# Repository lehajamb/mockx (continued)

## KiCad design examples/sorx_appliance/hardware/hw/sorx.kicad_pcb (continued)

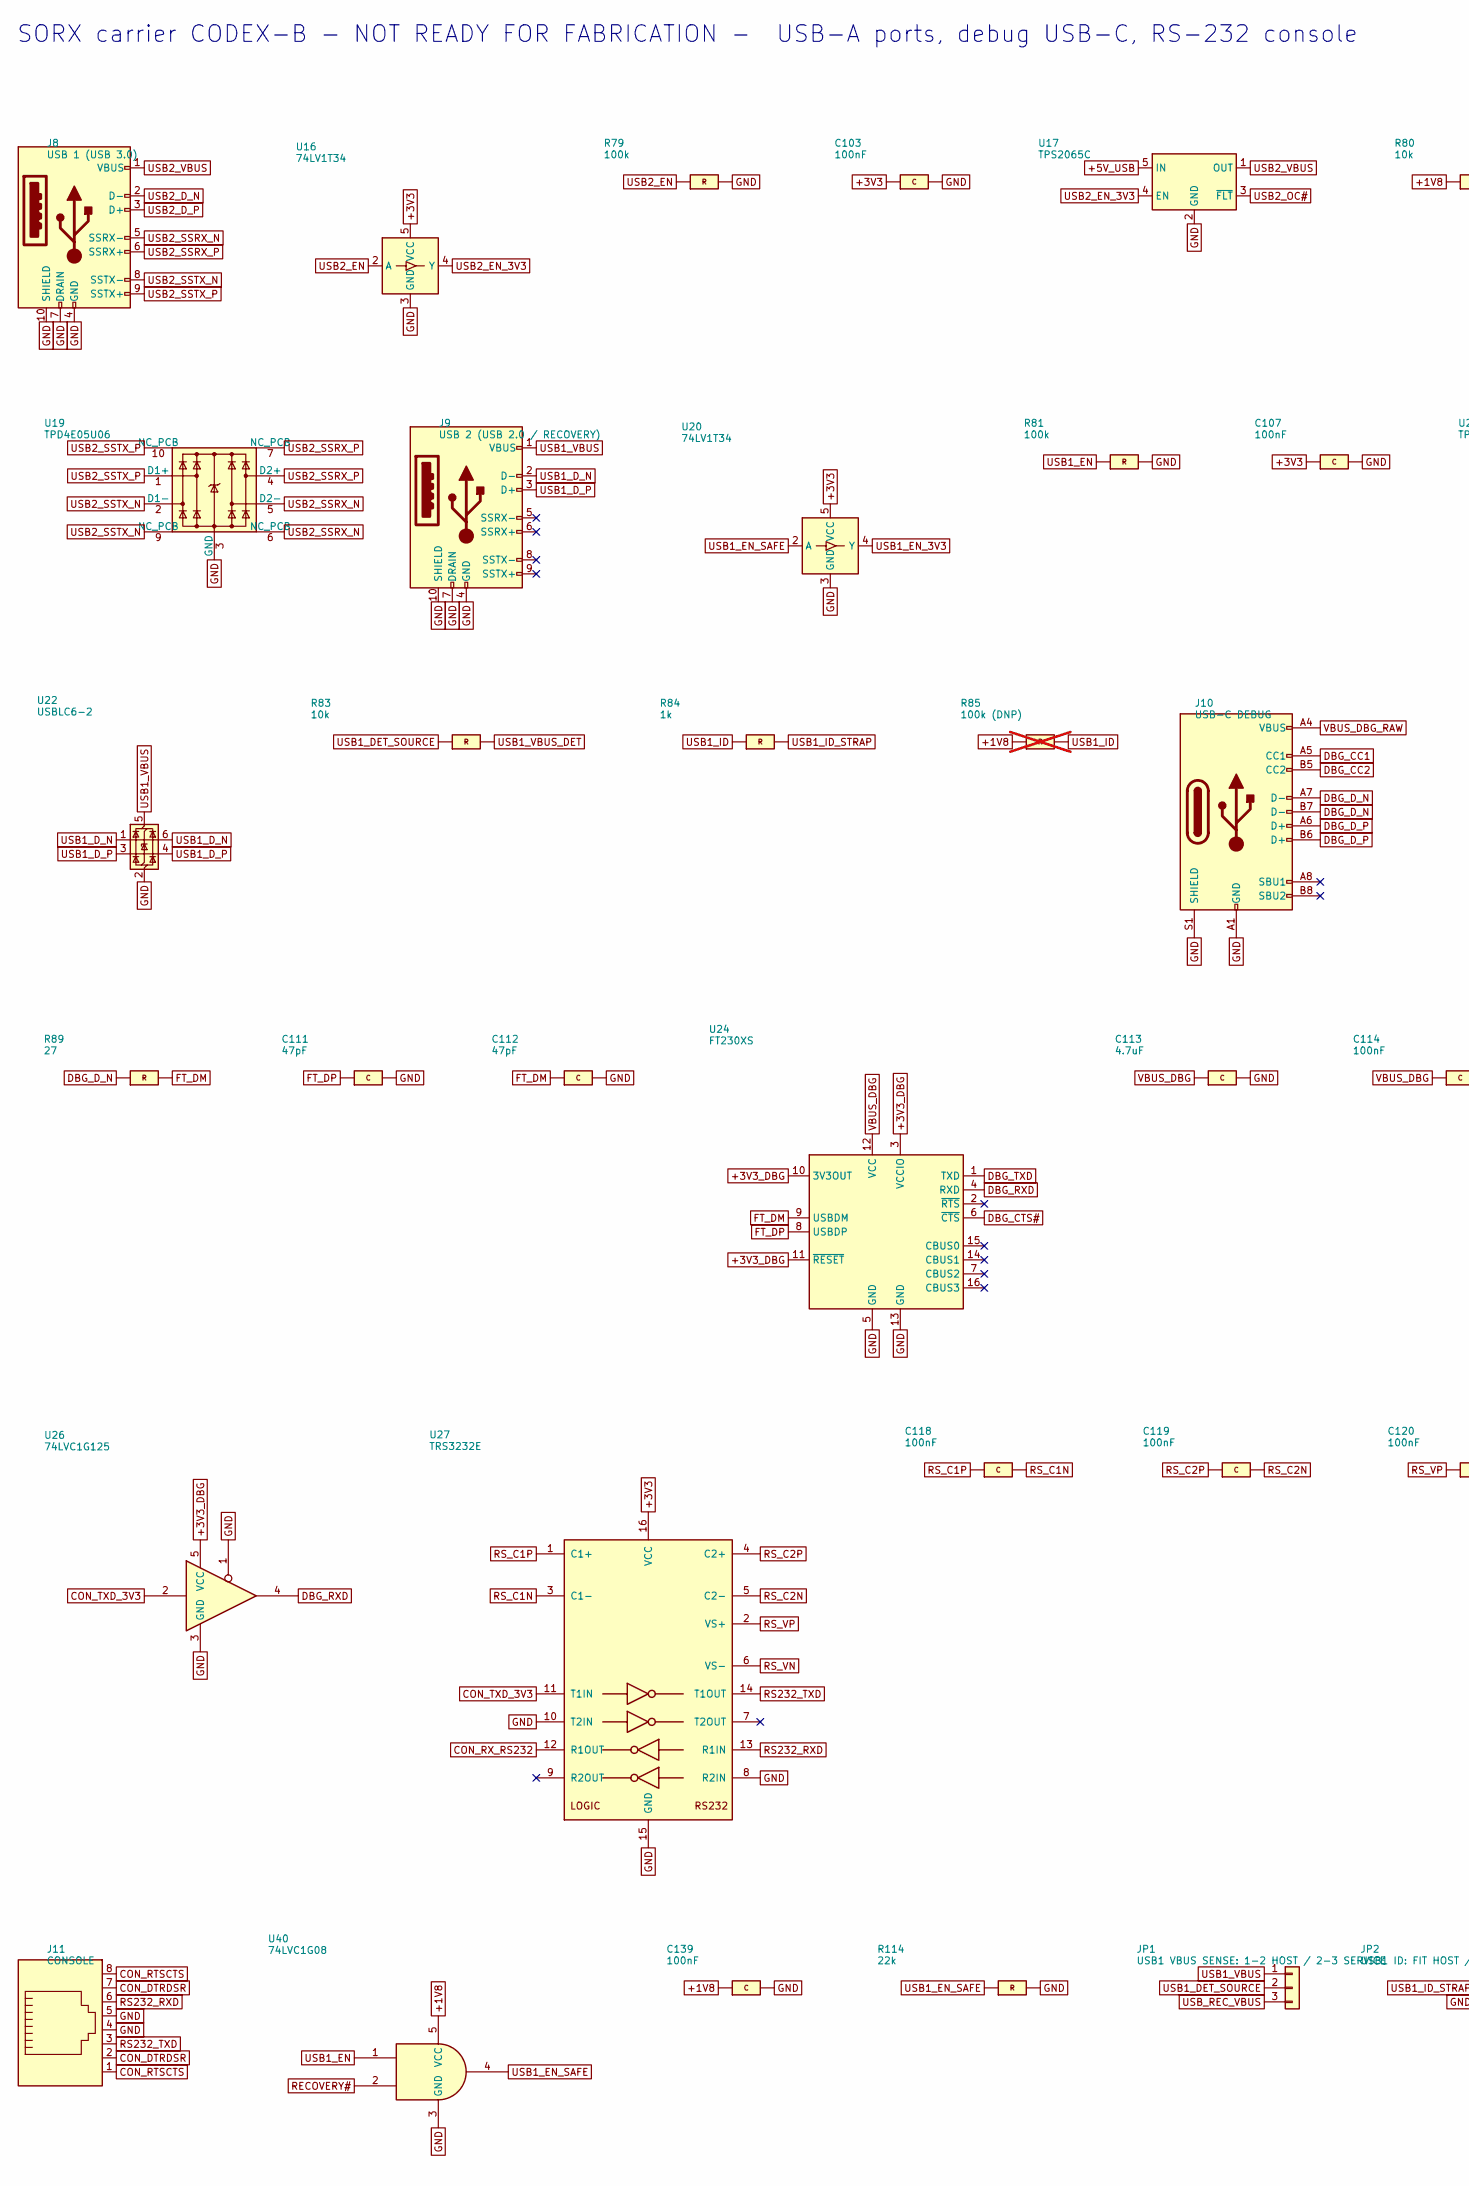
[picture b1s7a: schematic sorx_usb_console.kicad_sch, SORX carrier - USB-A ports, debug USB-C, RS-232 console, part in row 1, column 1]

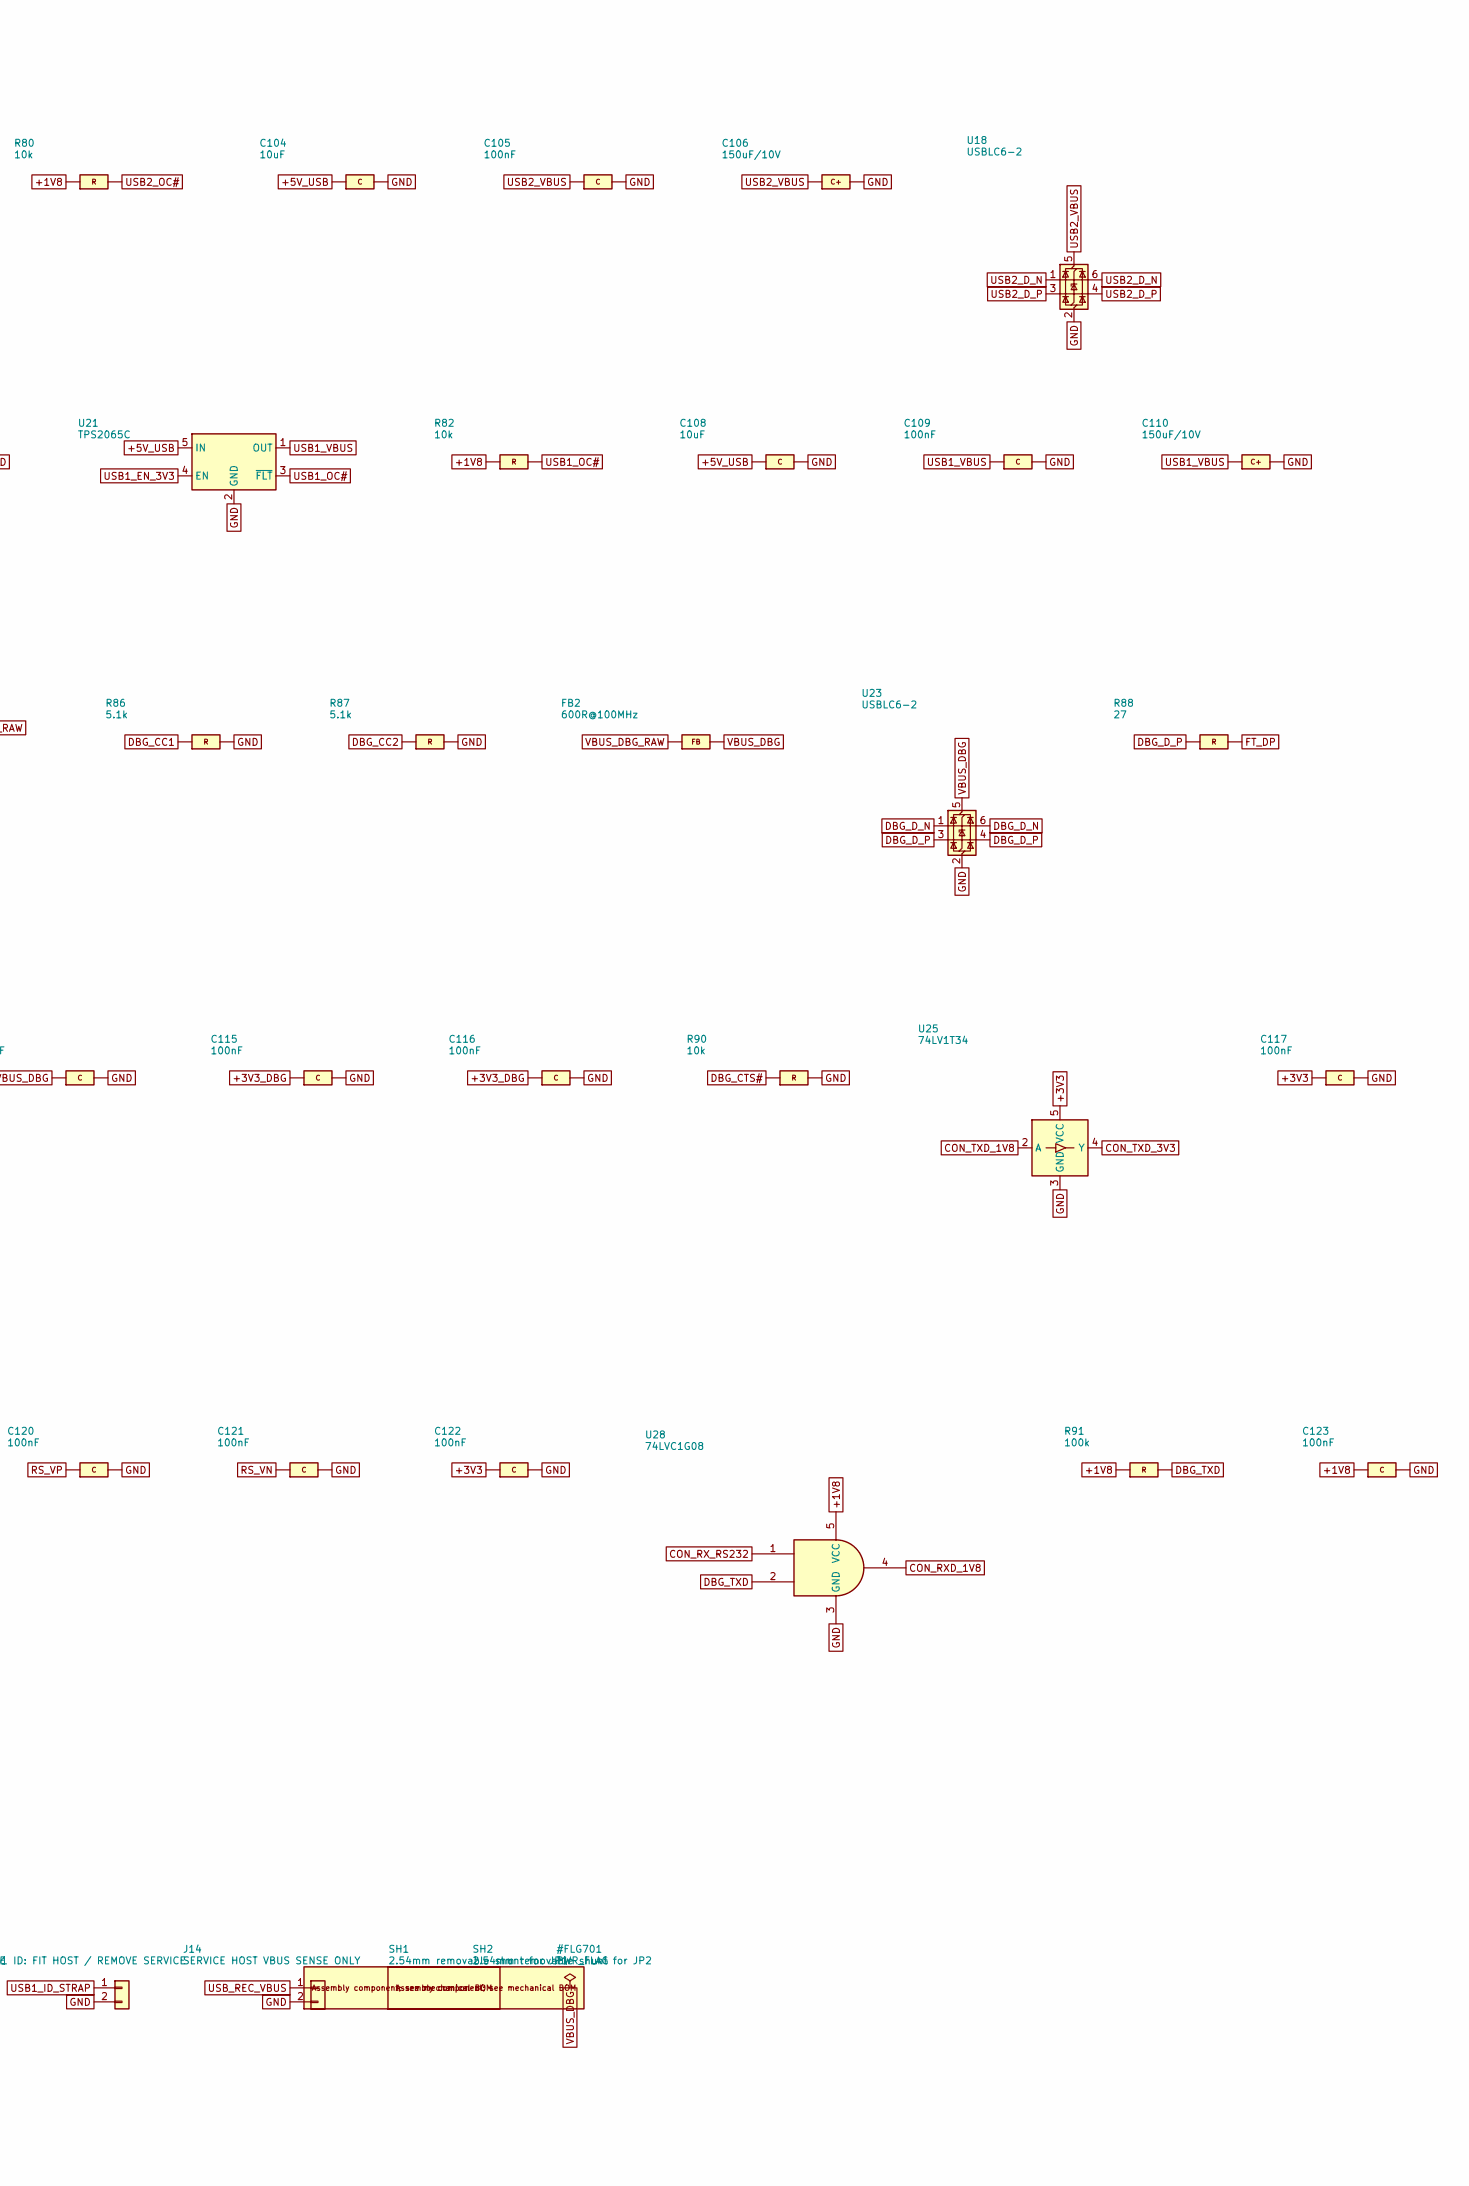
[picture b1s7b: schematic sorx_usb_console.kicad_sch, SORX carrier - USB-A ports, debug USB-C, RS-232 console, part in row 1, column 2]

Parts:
C103, C105, C107, C109, C114, C115, C116, C117, C118, C119, C120, C121, C122, C123, C139: 100nF; C_0402_1005Metric; MPN GRM155R71C104KA88D
C104, C108: 10uF; C_0805_2012Metric; MPN GRM21BR61A106KE19L
C106, C110: 150uF/10V; CP_Elec_6.3x7.7; MPN EEE-FK1A151P
C111, C112: 47pF; C_0402_1005Metric; MPN GRM1555C1H470JA01D
C113: 4.7uF; C_0603_1608Metric; MPN GRM188R61A475KE15D
FB2: 600R@100MHz; L_0603_1608Metric; MPN BLM18AG601SN1D
J8: USB 1 (USB 3.0); USB3_A_Receptacle_Wuerth_692122030100; MPN 692122030100
J9: USB 2 (USB 2.0 / RECOVERY); USB3_A_Receptacle_Wuerth_692122030100; MPN 692122030100
J10: USB-C DEBUG; USB_C_Receptacle_GCT_USB4105-xx-A_16P_TopMnt_Horizontal; MPN USB4105-GF-A
J11: CONSOLE; RJ45_Amphenol_54602-x08_Horizontal; MPN 54602-908LF
J14: SERVICE HOST VBUS SENSE ONLY; Wurth_61300211121; MPN 61300211121
JP1: USB1 VBUS SENSE: 1-2 HOST / 2-3 SERVICE; Wurth_61300311121; MPN 61300311121
JP2: USB1 ID: FIT HOST / REMOVE SERVICE; Wurth_61300211121; MPN 61300211121
R79, R81, R91: 100k; R_0402_1005Metric; MPN RC0402FR-07100KL
R80, R82, R83, R90: 10k; R_0402_1005Metric; MPN RC0402FR-0710KL
R84: 1k; R_0402_1005Metric; MPN RC0402FR-071KL
R85: 100k (DNP); R_0402_1005Metric; MPN RC0402FR-07100KL; not fitted
R86, R87: 5.1k; R_0402_1005Metric; MPN RC0402FR-075K1L
R88, R89: 27; R_0402_1005Metric; MPN RC0402FR-0727RL
R114: 22k; R_0402_1005Metric; MPN RC0402FR-0722KL
SH1: 2.54mm removable shunt for JP1; MPN 60900213421
SH2: 2.54mm removable shunt for JP2; MPN 60900213421
U16, U20, U25: 74LV1T34; SOT-23-5; MPN SN74LV1T34DBVR
U17, U21: TPS2065C; SOT-23-5; MPN TPS2065CDBVR
U18, U22, U23: USBLC6-2; SOT-23-6; MPN USBLC6-2SC6
U19: TPD4E05U06; USON-10_2.5x1.0mm_P0.5mm; MPN TPD4E05U06DQAR
U24: FT230XS; SSOP-16_3.9x4.9mm_P0.635mm; MPN FT230XS-R
U26: 74LVC1G125; SOT-23-5; MPN SN74LVC1G125DBVR
U27: TRS3232E; TSSOP-16_4.4x5mm_P0.65mm; MPN TRS3232EIPWR
U28, U40: 74LVC1G08; SOT-23-5; MPN SN74LVC1G08DBVR

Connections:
+1V8: C123.1, C139.1, R80.1, R82.1, R85.1, R91.1, U28.5 (VCC), U40.5 (VCC); also elsewhere on the board
+3V3: C103.1, C107.1, C117.1, C122.1, U16.5 (VCC), U20.5 (VCC), U25.5 (VCC), U27.16 (VCC); also elsewhere on the board
+3V3_DBG: C115.1, C116.1, U24.3 (VCCIO), U24.10 (3V3OUT), U24.11 (~RESET), U26.5 (VCC)
+5V_USB: C104.1, C108.1, U17.5 (IN), U21.5 (IN); also elsewhere on the board
CON_DTRDSR: J11.2, J11.7
CON_RTSCTS: J11.1, J11.8
CON_RXD_1V8: U28.4; also elsewhere on the board
CON_RX_RS232: U27.12 (R1OUT), U28.1
CON_TXD_1V8: U25.2 (A); also elsewhere on the board
CON_TXD_3V3: U25.4 (Y), U26.2, U27.11 (T1IN)
DBG_CC1: J10.A5 (CC1), R86.1
DBG_CC2: J10.B5 (CC2), R87.1
DBG_CTS#: R90.1, U24.6 (~CTS)
DBG_D_N: J10.A7 (D-), J10.B7 (D-), R89.1, U23.1 (I/O1), U23.6 (I/O1)
DBG_D_P: J10.A6 (D+), J10.B6 (D+), R88.1, U23.3 (I/O2), U23.4 (I/O2)
DBG_RXD: U24.4 (RXD), U26.4
DBG_TXD: R91.2, U24.1 (TXD), U28.2
FT_DM: C112.1, R89.2, U24.9 (USBDM)
FT_DP: C111.1, R88.2, U24.8 (USBDP)
GND: C103.2, C104.2, C105.2, C106.2 (-), C107.2, C108.2, C109.2, C110.2 (-), C111.2, C112.2, C113.2, C114.2, C115.2, C116.2, C117.2, C120.2, C121.2, C122.2, C123.2, C139.2, J8.4 (GND), J8.7 (DRAIN), J8.10 (SHIELD), J9.4 (GND), J9.7 (DRAIN), J9.10 (SHIELD), J10.A1 (GND), J10.A12 (GND), J10.B1 (GND), J10.B12 (GND), J10.S1 (SHIELD), J11.4, J11.5, J14.2, JP2.2, R79.2, R81.2, R86.2, R87.2, R90.2, R114.2, U16.3 (GND), U17.2 (GND), U18.2 (GND), U19.3 (GND), U19.8 (GND), U20.3 (GND), U21.2 (GND), U22.2 (GND), U23.2 (GND), U24.5 (GND), U24.13 (GND), U25.3 (GND), U26.1, U26.3 (GND), U27.8 (R2IN), U27.10 (T2IN), U27.15 (GND), U28.3 (GND), U40.3 (GND); also elsewhere on the board
RECOVERY#: U40.2; also elsewhere on the board
RS232_RXD: J11.6, U27.13 (R1IN)
RS232_TXD: J11.3, U27.14 (T1OUT)
RS_C1N: C118.2, U27.3 (C1-)
RS_C1P: C118.1, U27.1 (C1+)
RS_C2N: C119.2, U27.5 (C2-)
RS_C2P: C119.1, U27.4 (C2+)
RS_VN: C121.1, U27.6 (VS-)
RS_VP: C120.1, U27.2 (VS+)
USB1_DET_SOURCE: JP1.2, R83.1
USB1_D_N: J9.2 (D-), U22.1 (I/O1), U22.6 (I/O1); also elsewhere on the board
USB1_D_P: J9.3 (D+), U22.3 (I/O2), U22.4 (I/O2); also elsewhere on the board
USB1_EN: R81.1, U40.1; also elsewhere on the board
USB1_EN_3V3: U20.4 (Y), U21.4 (EN)
USB1_EN_SAFE: R114.1, U20.2 (A), U40.4
USB1_ID: R84.1, R85.2; also elsewhere on the board
USB1_ID_STRAP: JP2.1, R84.2
USB1_OC#: R82.2, U21.3 (~FLT); also elsewhere on the board
USB1_VBUS: C109.1, C110.1 (+), J9.1 (VBUS), JP1.1, U21.1 (OUT), U22.5 (VBUS)
USB1_VBUS_DET: R83.2; also elsewhere on the board
USB2_D_N: J8.2 (D-), U18.1 (I/O1), U18.6 (I/O1); also elsewhere on the board
USB2_D_P: J8.3 (D+), U18.3 (I/O2), U18.4 (I/O2); also elsewhere on the board
USB2_EN: R79.1, U16.2 (A); also elsewhere on the board
USB2_EN_3V3: U16.4 (Y), U17.4 (EN)
USB2_OC#: R80.2, U17.3 (~FLT); also elsewhere on the board
USB2_SSRX_N: J8.5 (SSRX-), U19.5 (D2-), U19.6 (NC_PCB); also elsewhere on the board
USB2_SSRX_P: J8.6 (SSRX+), U19.4 (D2+), U19.7 (NC_PCB); also elsewhere on the board
USB2_SSTX_N: J8.8 (SSTX-), U19.2 (D1-), U19.9 (NC_PCB); also elsewhere on the board
USB2_SSTX_P: J8.9 (SSTX+), U19.1 (D1+), U19.10 (NC_PCB); also elsewhere on the board
USB2_VBUS: C105.1, C106.1 (+), J8.1 (VBUS), U17.1 (OUT), U18.5 (VBUS)
USB_REC_VBUS: J14.1, JP1.3
VBUS_DBG: C113.1, C114.1, FB2.2, U23.5 (VBUS), U24.12 (VCC)
VBUS_DBG_RAW: FB2.1, J10.A4 (VBUS), J10.A9 (VBUS), J10.B4 (VBUS), J10.B9 (VBUS)

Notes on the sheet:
SORX carrier CODEX-B - NOT READY FOR FABRICATION - USB-A ports, debug USB-C, RS-232 console

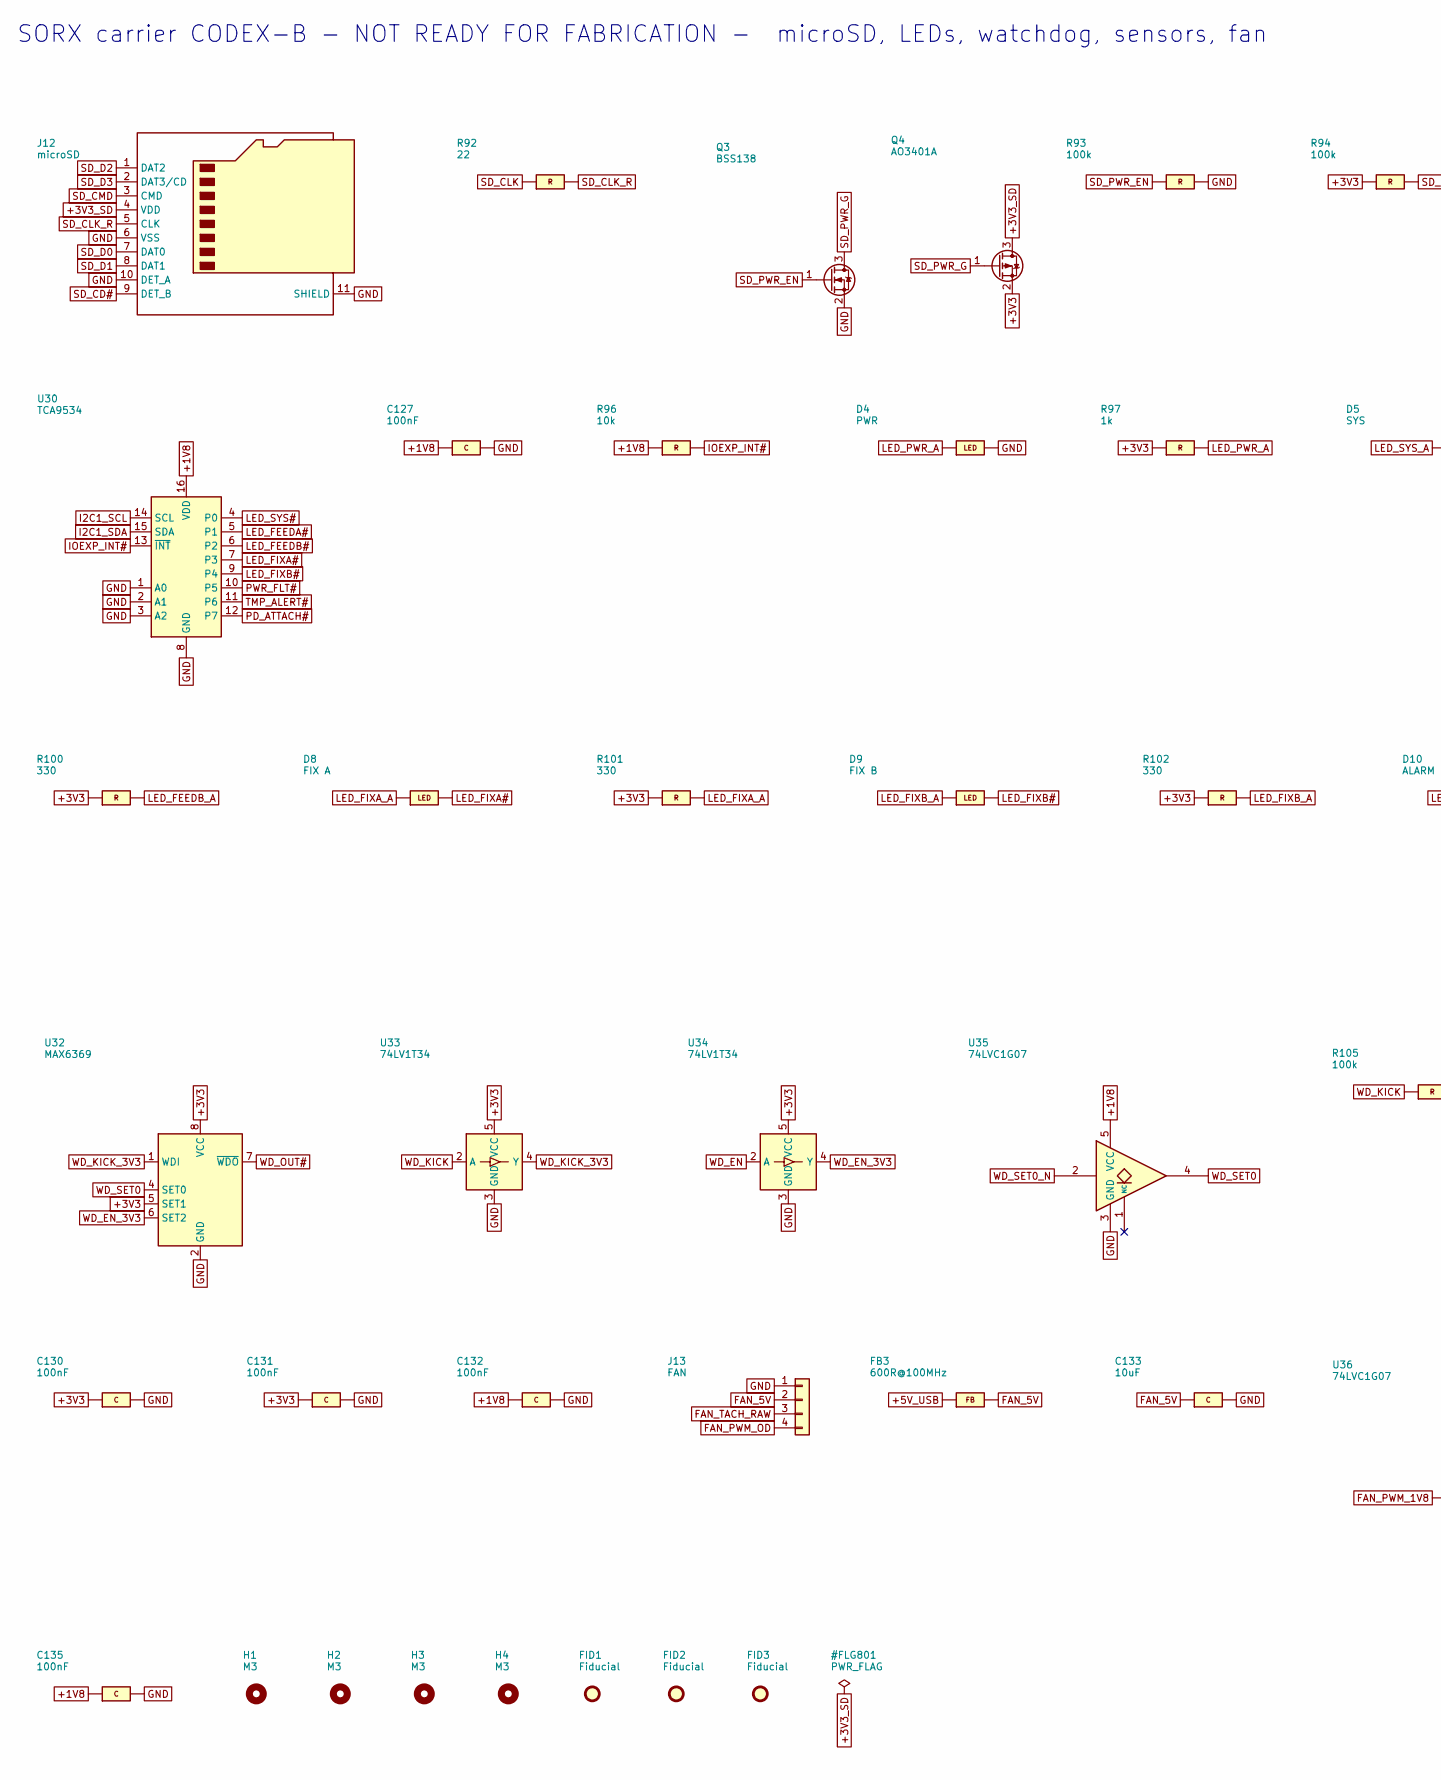
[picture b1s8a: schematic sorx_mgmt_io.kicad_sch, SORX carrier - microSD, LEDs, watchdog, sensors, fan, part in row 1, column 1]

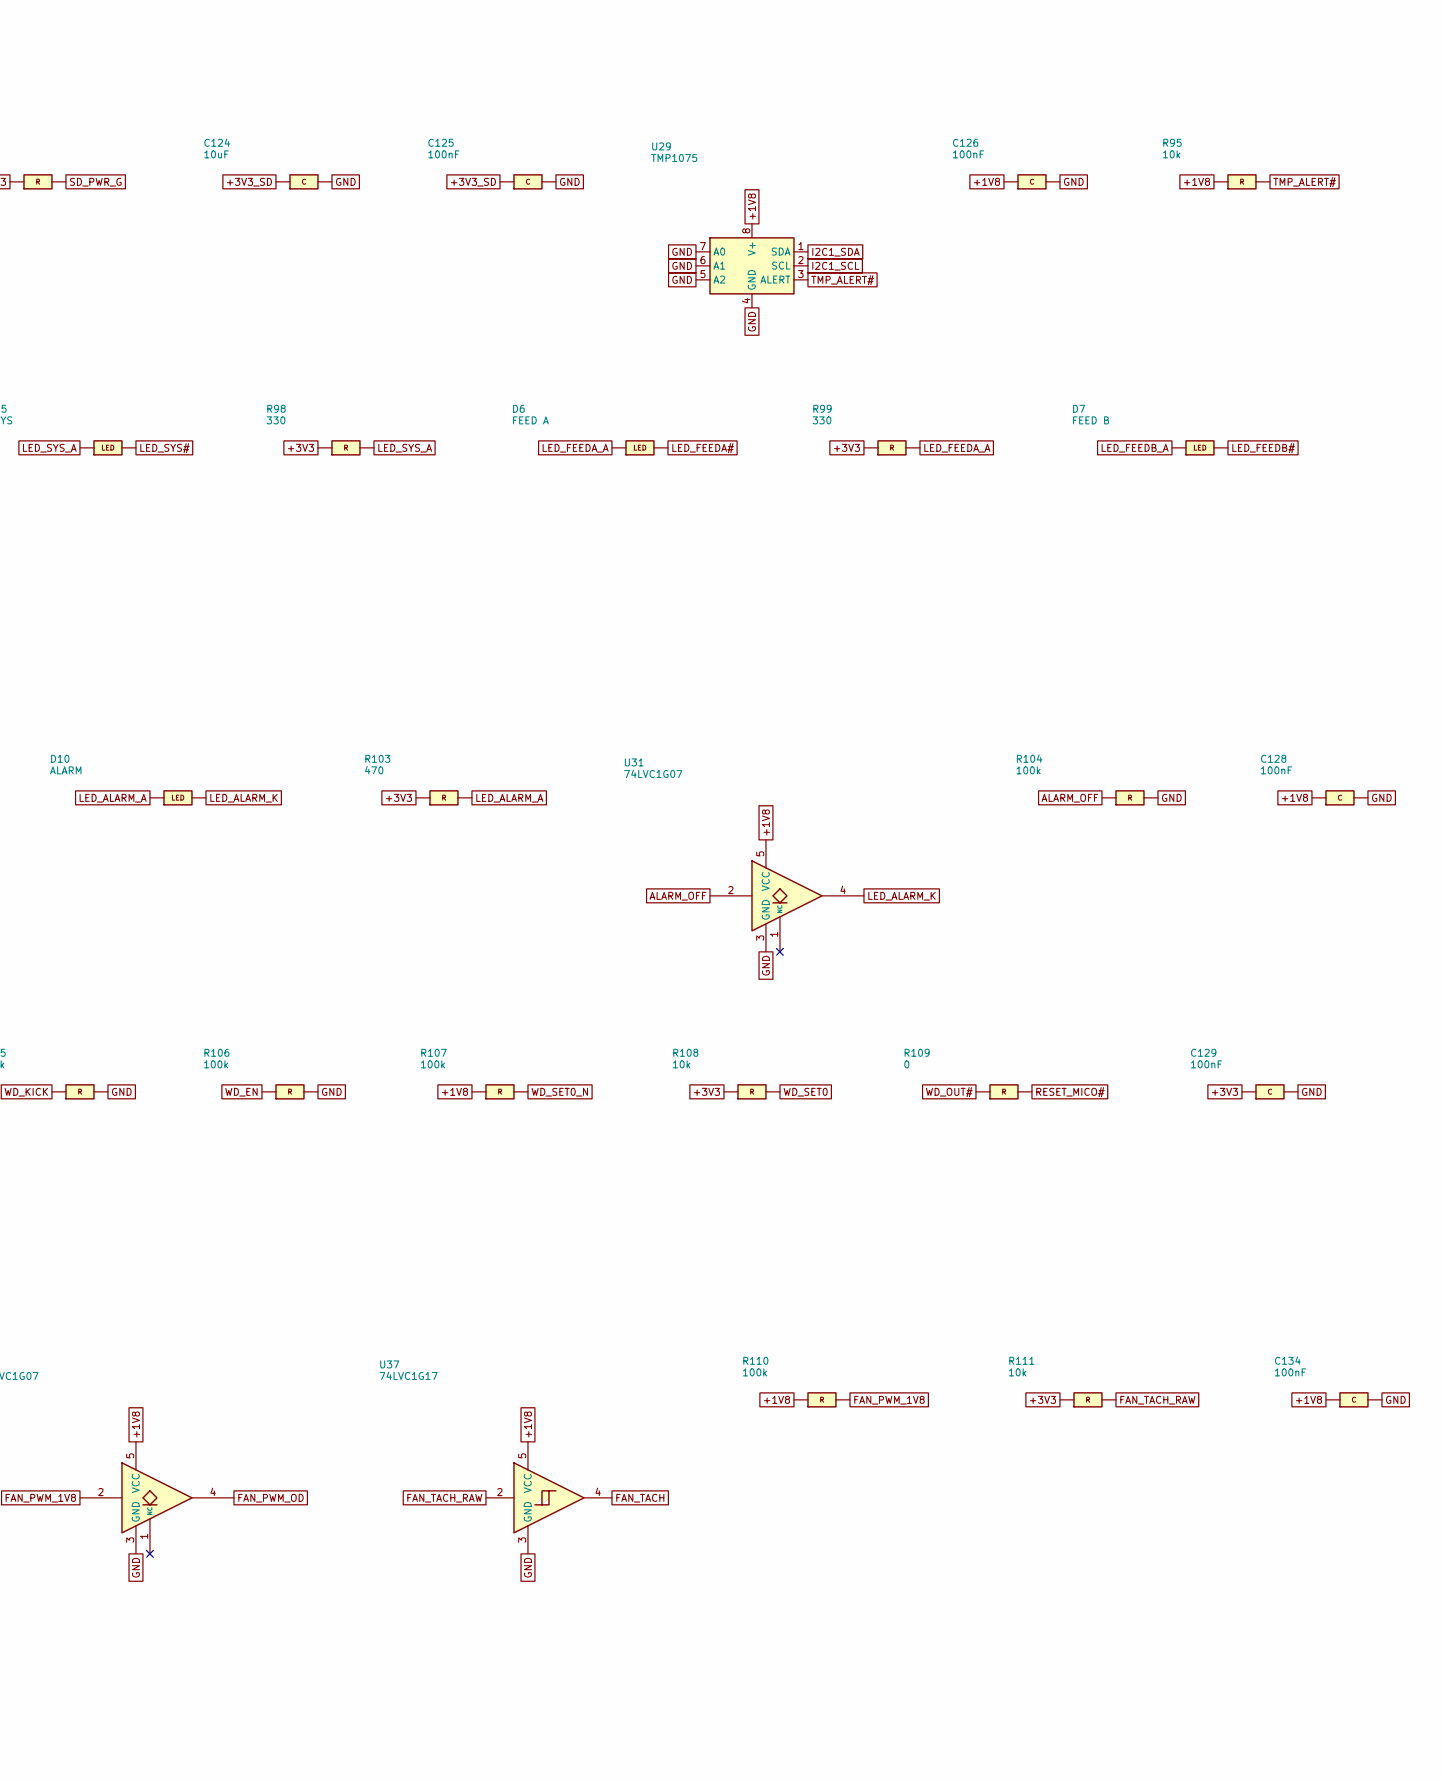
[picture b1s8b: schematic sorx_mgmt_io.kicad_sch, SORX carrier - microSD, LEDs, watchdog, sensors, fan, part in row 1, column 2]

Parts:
C124, C133: 10uF; C_0805_2012Metric; MPN GRM21BR61A106KE19L
C125, C126, C127, C128, C129, C130, C131, C132, C134, C135: 100nF; C_0402_1005Metric; MPN GRM155R71C104KA88D
D4: PWR; LED_Kingbright_KPA-3010_3x2x1mm; MPN KPA-3010SGC
D5: SYS; LED_Kingbright_KPA-3010_3x2x1mm; MPN KPA-3010SGC
D6: FEED A; LED_Kingbright_KPA-3010_3x2x1mm; MPN KPA-3010SGC
D7: FEED B; LED_Kingbright_KPA-3010_3x2x1mm; MPN KPA-3010SGC
D8: FIX A; LED_Kingbright_KPA-3010_3x2x1mm; MPN KPA-3010YC
D9: FIX B; LED_Kingbright_KPA-3010_3x2x1mm; MPN KPA-3010YC
D10: ALARM; LED_Kingbright_KPA-3010_3x2x1mm; MPN KPA-3010EC
FB3: 600R@100MHz; L_0603_1608Metric; MPN BLM18AG601SN1D
FID1, FID2, FID3: Fiducial; Fiducial_1mm_Mask2mm
H1, H2, H3, H4: M3; MountingHole_3.2mm_M3
J12: microSD; microSD_HC_Hirose_DM3AT-SF-PEJM5; MPN DM3AT-SF-PEJM5
J13: FAN; FanPinHeader_1x04_P2.54mm_Vertical; MPN 47053-1000
Q3: BSS138; SOT-23; MPN BSS138LT1G
Q4: AO3401A; SOT-23; MPN AO3401A
R92: 22; R_0402_1005Metric; MPN RC0402FR-0722RL
R93, R94, R104, R105, R106, R107, R110: 100k; R_0402_1005Metric; MPN RC0402FR-07100KL
R95, R96, R108, R111: 10k; R_0402_1005Metric; MPN RC0402FR-0710KL
R97: 1k; R_0402_1005Metric; MPN RC0402FR-071KL
R98, R99, R100, R101, R102: 330; R_0402_1005Metric; MPN RC0402FR-07330RL
R103: 470; R_0402_1005Metric; MPN RC0402FR-07470RL
R109: 0; R_0402_1005Metric; MPN RC0402JR-070RL
U29: TMP1075; SOIC-8_3.9x4.9mm_P1.27mm; MPN TMP1075DR
U30: TCA9534; TSSOP-16_4.4x5mm_P0.65mm; MPN TCA9534PWR
U31, U35, U36: 74LVC1G07; SOT-23-5; MPN SN74LVC1G07DBVR
U32: MAX6369; SOT-23-8; MPN MAX6369KA+T
U33, U34: 74LV1T34; SOT-23-5; MPN SN74LV1T34DBVR
U37: 74LVC1G17; SOT-23-5; MPN SN74LVC1G17DBVR

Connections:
+1V8: C126.1, C127.1, C128.1, C132.1, C134.1, C135.1, R95.1, R96.1, R107.1, R110.1, U29.8 (V+), U30.16 (VDD), U31.5 (VCC), U35.5 (VCC), U36.5 (VCC), U37.5 (VCC); also elsewhere on the board
+3V3: C129.1, C130.1, C131.1, Q4.2 (S), R94.1, R97.1, R98.1, R99.1, R100.1, R101.1, R102.1, R103.1, R108.1, R111.1, U32.5 (SET1), U32.8 (VCC), U33.5 (VCC), U34.5 (VCC); also elsewhere on the board
+3V3_SD: C124.1, C125.1, J12.4 (VDD), Q4.3 (D)
+5V_USB: FB3.1; also elsewhere on the board
ALARM_OFF: R104.1, U31.2; also elsewhere on the board
FAN_5V: C133.1, FB3.2, J13.2
FAN_PWM_1V8: R110.2, U36.2; also elsewhere on the board
FAN_PWM_OD: J13.4, U36.4
FAN_TACH: U37.4; also elsewhere on the board
FAN_TACH_RAW: J13.3, R111.2, U37.2
GND: C124.2, C125.2, C126.2, C127.2, C128.2, C129.2, C130.2, C131.2, C132.2, C133.2, C134.2, C135.2, D4.1 (K), J12.6 (VSS), J12.10 (DET_A), J12.11 (SHIELD), J13.1, Q3.2 (S), R93.2, R104.2, R105.2, R106.2, U29.4 (GND), U29.5 (A2), U29.6 (A1), U29.7 (A0), U30.1 (A0), U30.2 (A1), U30.3 (A2), U30.8 (GND), U31.3 (GND), U32.2 (GND), U33.3 (GND), U34.3 (GND), U35.3 (GND), U36.3 (GND), U37.3 (GND); also elsewhere on the board
I2C1_SCL: U29.2 (SCL), U30.14 (SCL); also elsewhere on the board
I2C1_SDA: U29.1 (SDA), U30.15 (SDA); also elsewhere on the board
IOEXP_INT#: R96.2, U30.13 (~INT); also elsewhere on the board
LED_ALARM_A: D10.2 (A), R103.2
LED_ALARM_K: D10.1 (K), U31.4
LED_FEEDA#: D6.1 (K), U30.5 (P1)
LED_FEEDA_A: D6.2 (A), R99.2
LED_FEEDB#: D7.1 (K), U30.6 (P2)
LED_FEEDB_A: D7.2 (A), R100.2
LED_FIXA#: D8.1 (K), U30.7 (P3)
LED_FIXA_A: D8.2 (A), R101.2
LED_FIXB#: D9.1 (K), U30.9 (P4)
LED_FIXB_A: D9.2 (A), R102.2
LED_PWR_A: D4.2 (A), R97.2
LED_SYS#: D5.1 (K), U30.4 (P0)
LED_SYS_A: D5.2 (A), R98.2
PD_ATTACH#: U30.12 (P7); also elsewhere on the board
PWR_FLT#: U30.10 (P5); also elsewhere on the board
RESET_MICO#: R109.2; also elsewhere on the board
SD_CD#: J12.9 (DET_B); also elsewhere on the board
SD_CLK: R92.1; also elsewhere on the board
SD_CLK_R: J12.5 (CLK), R92.2
SD_CMD: J12.3 (CMD); also elsewhere on the board
SD_D0: J12.7 (DAT0); also elsewhere on the board
SD_D1: J12.8 (DAT1); also elsewhere on the board
SD_D2: J12.1 (DAT2); also elsewhere on the board
SD_D3: J12.2 (DAT3/CD); also elsewhere on the board
SD_PWR_EN: Q3.1 (G), R93.1; also elsewhere on the board
SD_PWR_G: Q3.3 (D), Q4.1 (G), R94.2
TMP_ALERT#: R95.2, U29.3 (ALERT), U30.11 (P6)
WD_EN: R106.1, U34.2 (A); also elsewhere on the board
WD_EN_3V3: U32.6 (SET2), U34.4 (Y)
WD_KICK: R105.1, U33.2 (A); also elsewhere on the board
WD_KICK_3V3: U32.1 (WDI), U33.4 (Y)
WD_OUT#: R109.1, U32.7 (~WDO)
WD_SET0: R108.2, U32.4 (SET0), U35.4
WD_SET0_N: R107.2, U35.2; also elsewhere on the board

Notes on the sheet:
SORX carrier CODEX-B - NOT READY FOR FABRICATION - microSD, LEDs, watchdog, sensors, fan

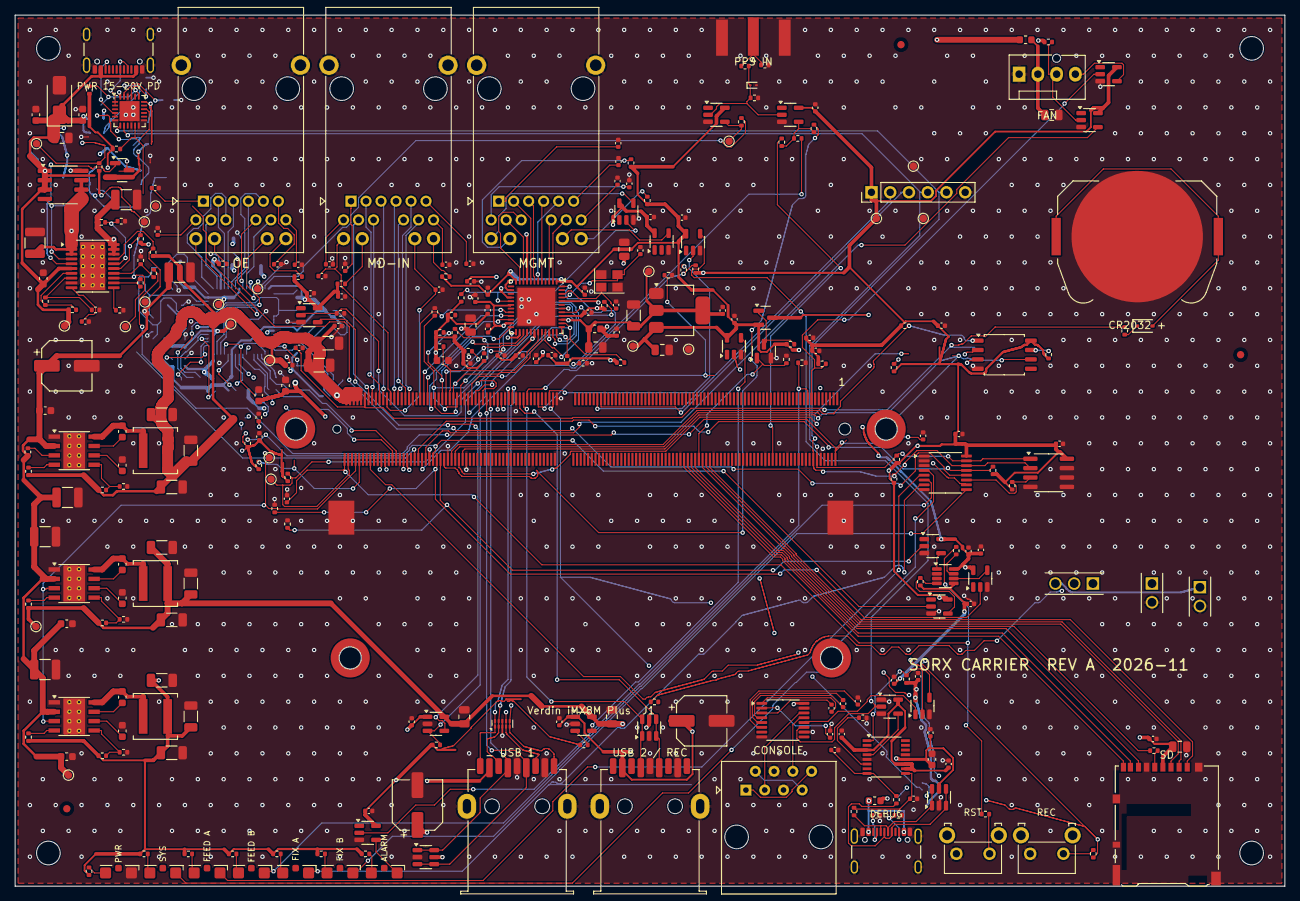
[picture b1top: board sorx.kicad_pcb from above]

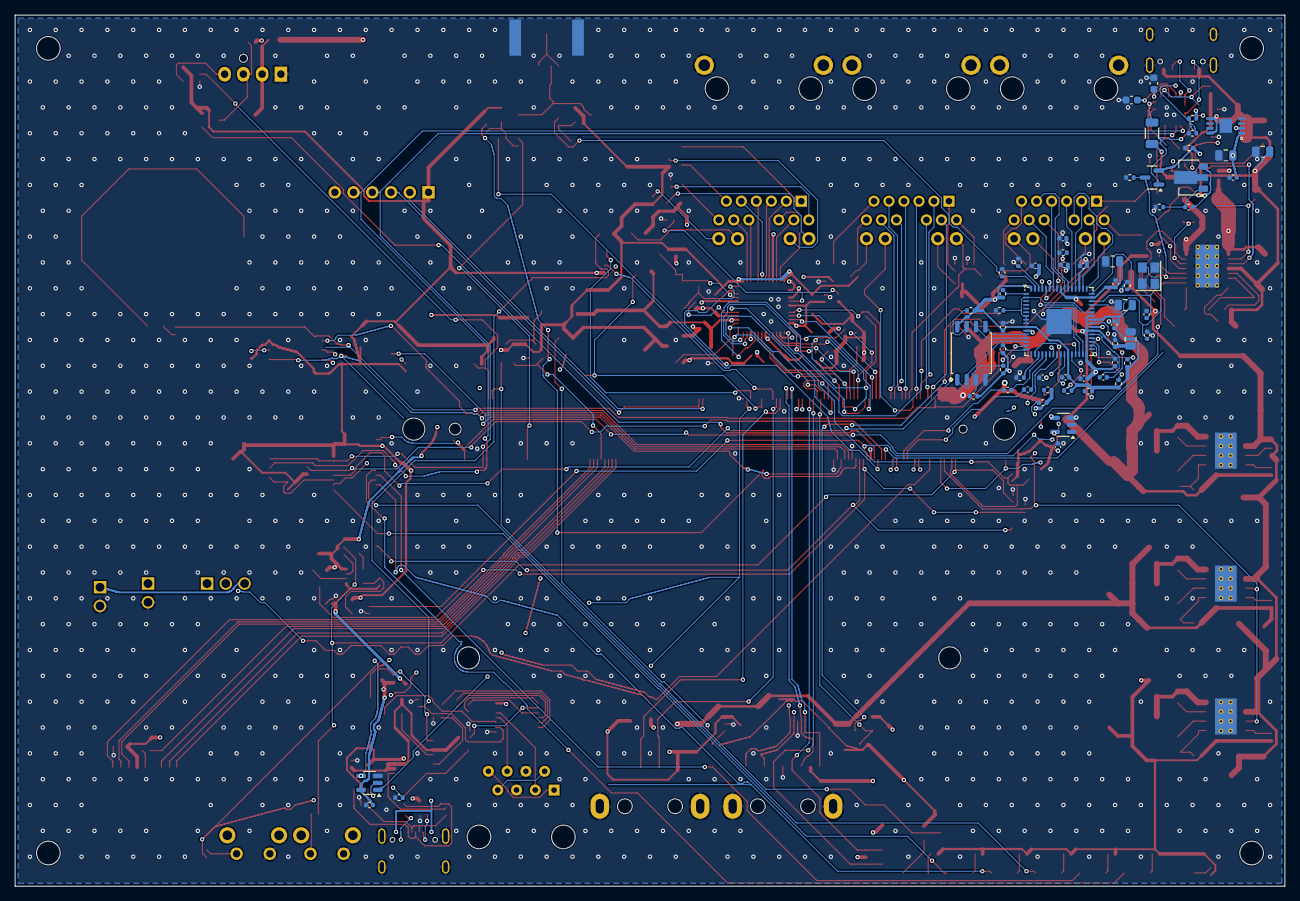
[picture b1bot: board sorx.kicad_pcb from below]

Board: 6 copper layers, 172.0 x 118.0 mm, 371 parts (60 on the bottom side), 269 nets.
